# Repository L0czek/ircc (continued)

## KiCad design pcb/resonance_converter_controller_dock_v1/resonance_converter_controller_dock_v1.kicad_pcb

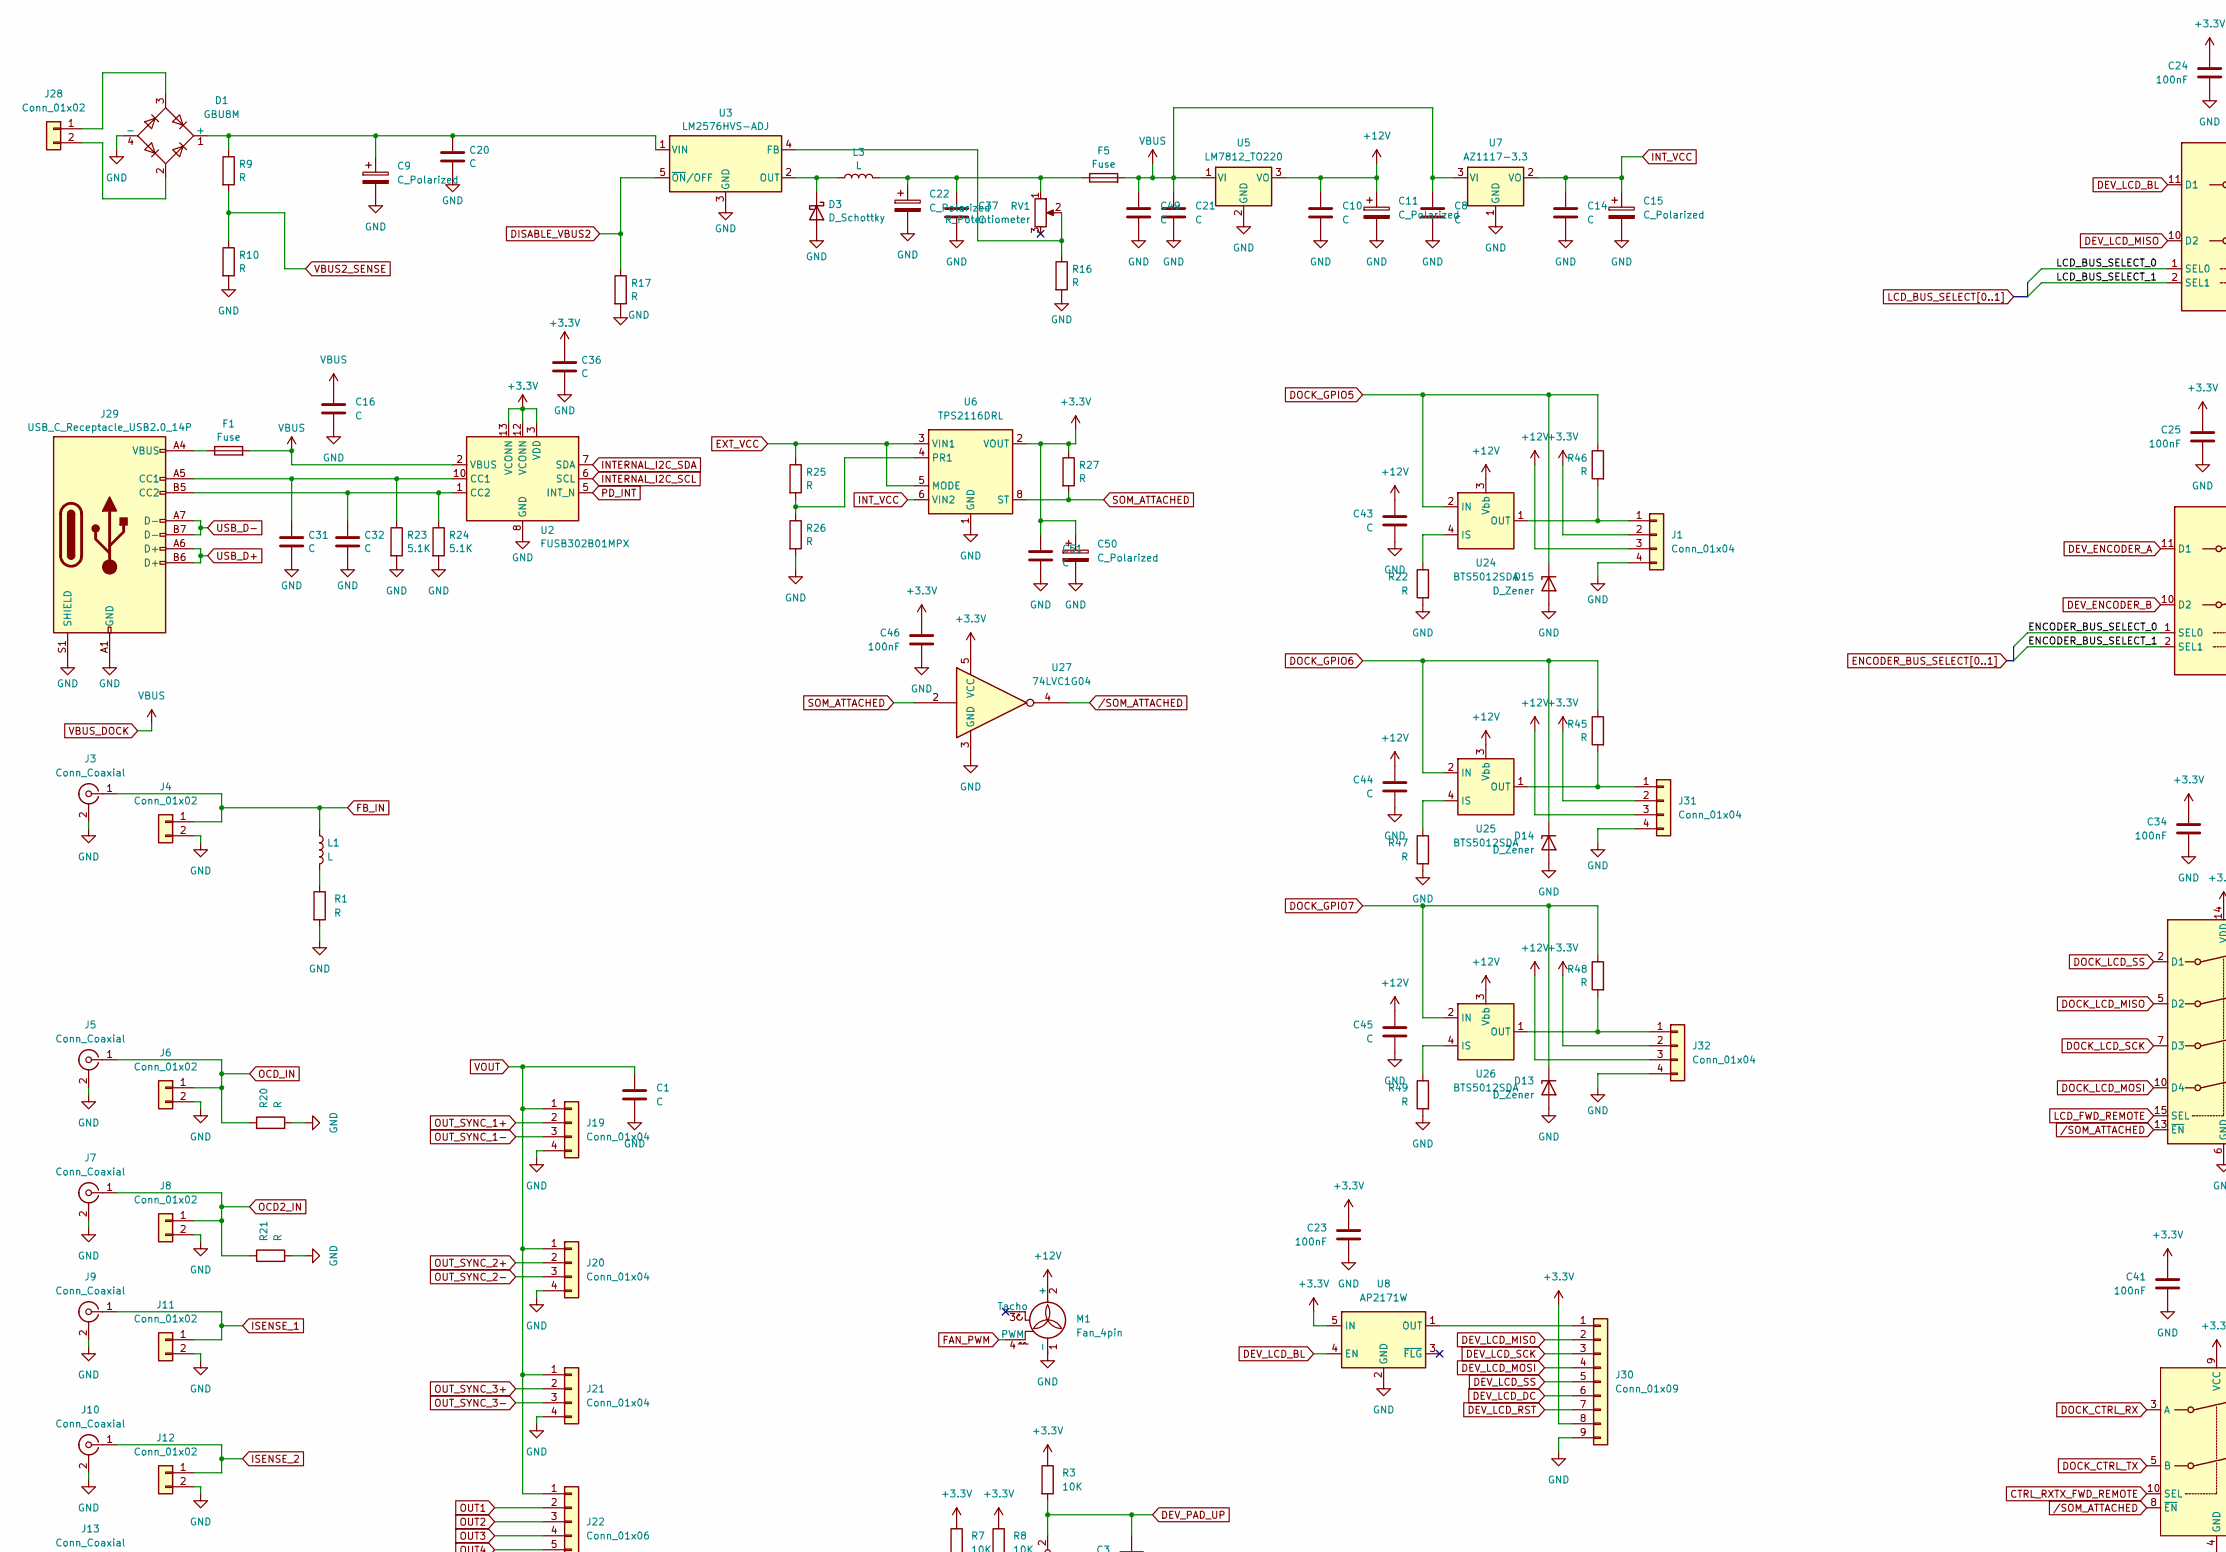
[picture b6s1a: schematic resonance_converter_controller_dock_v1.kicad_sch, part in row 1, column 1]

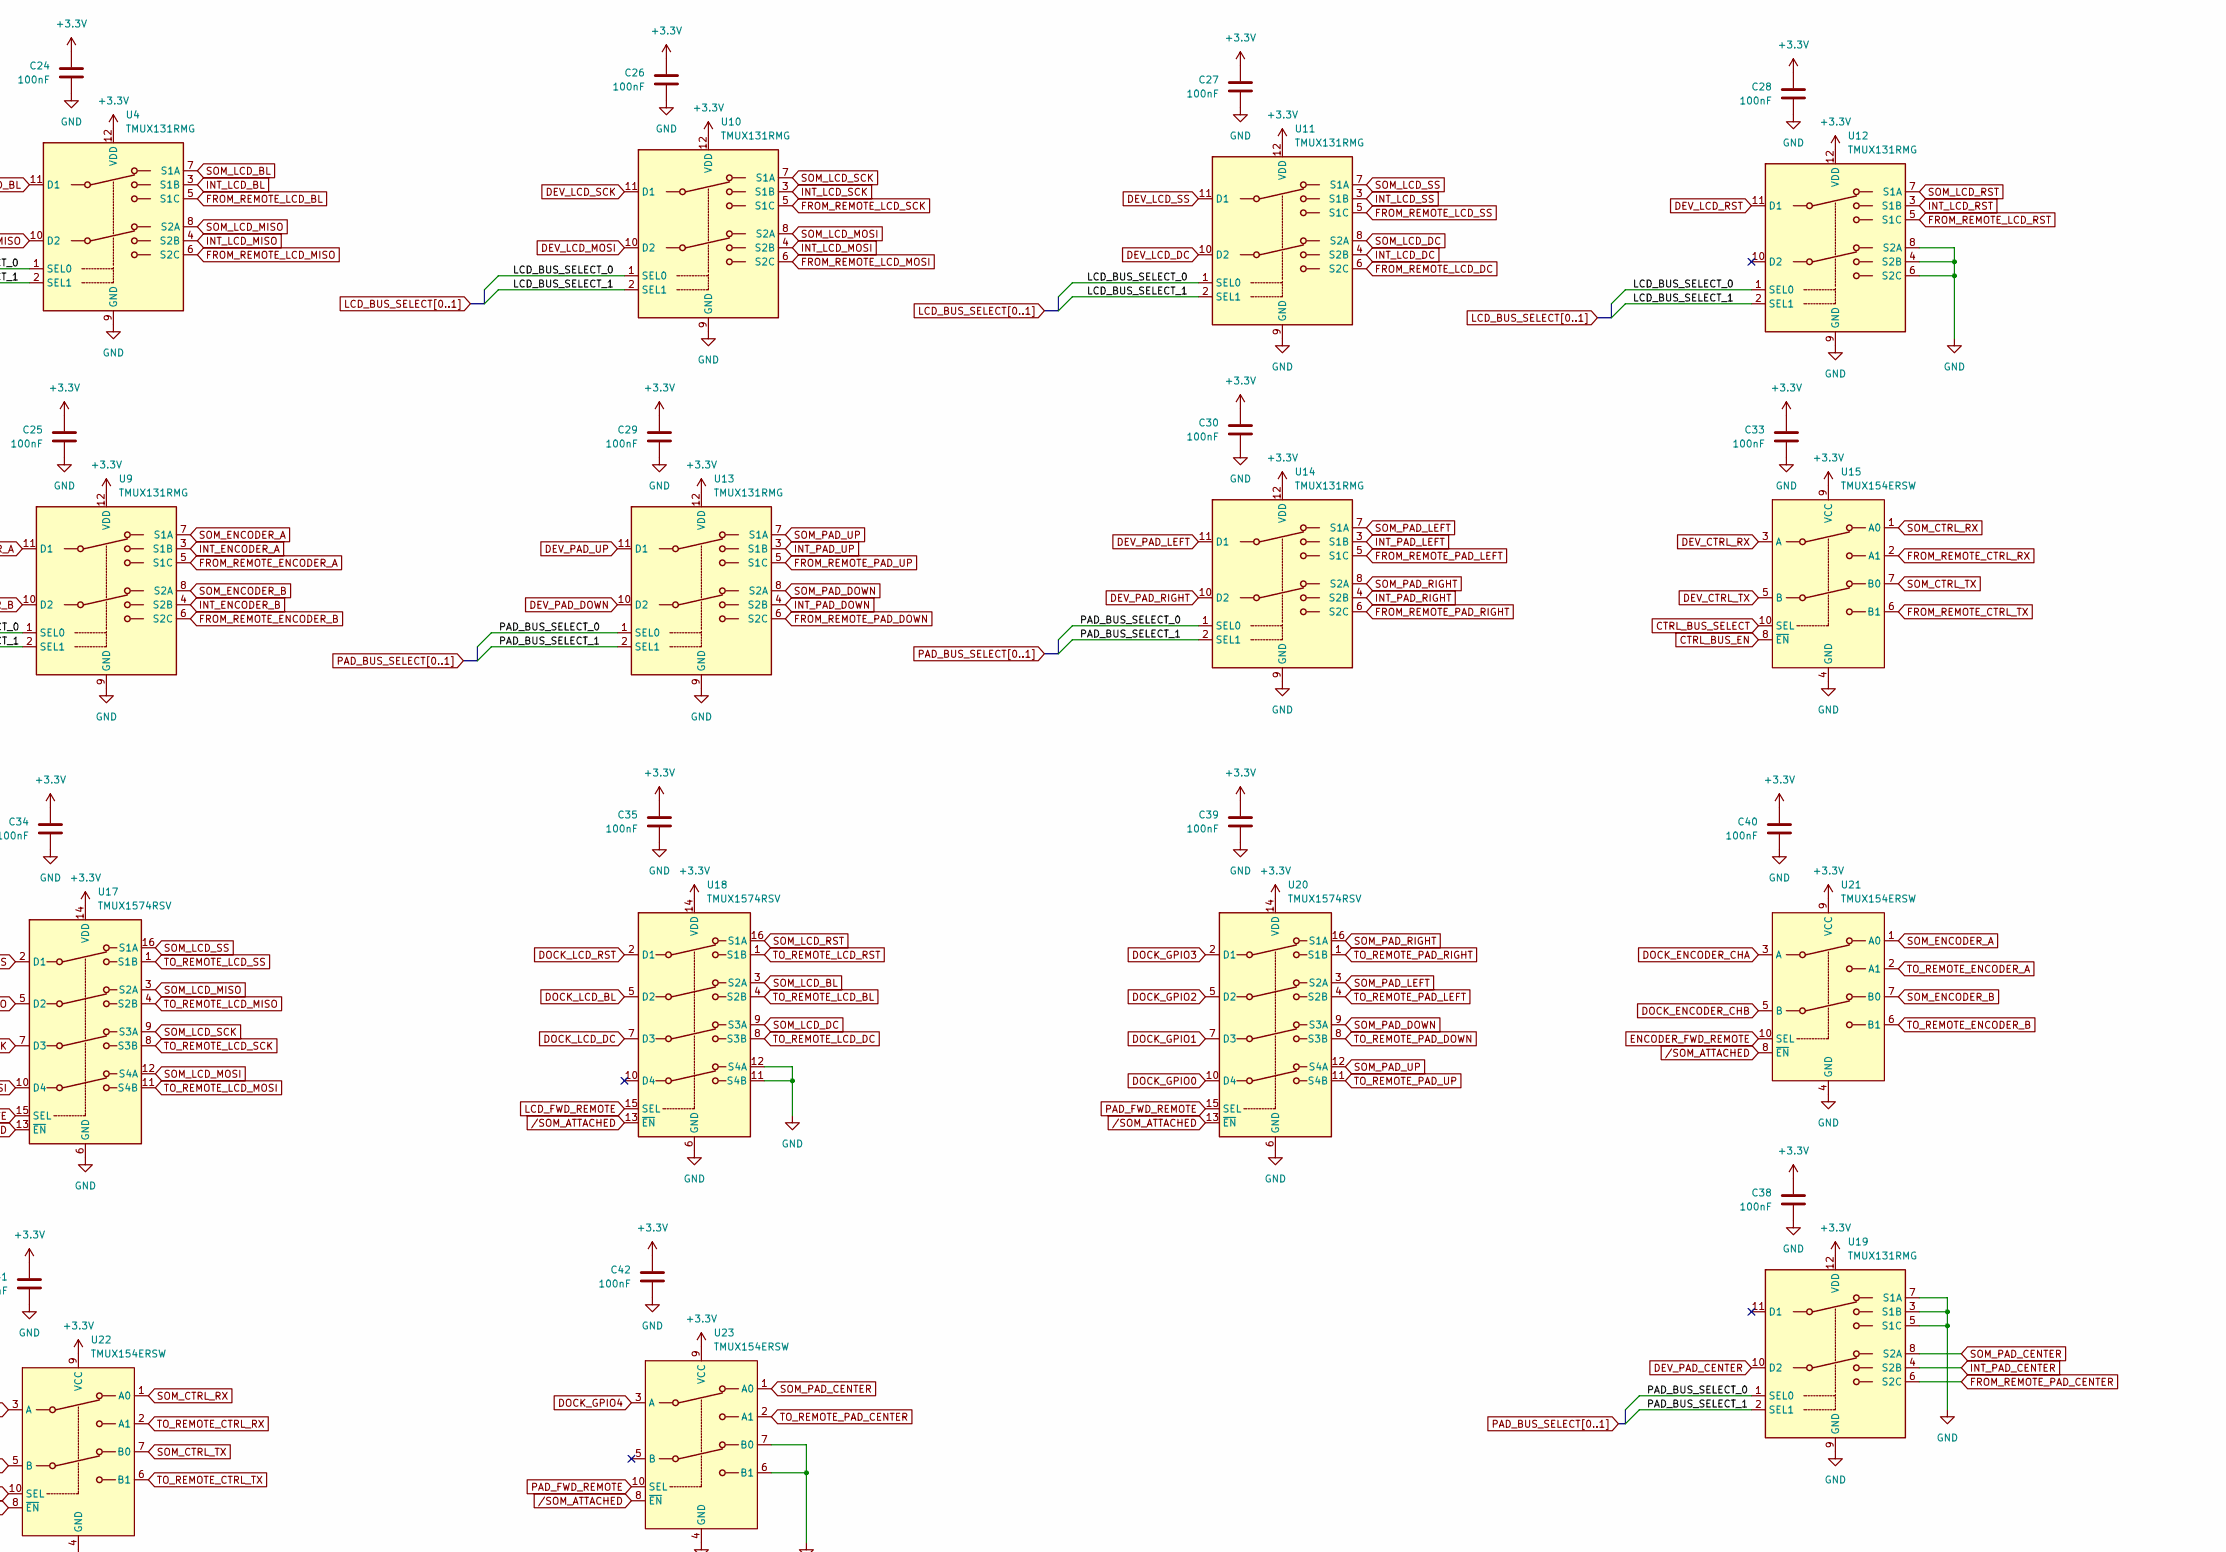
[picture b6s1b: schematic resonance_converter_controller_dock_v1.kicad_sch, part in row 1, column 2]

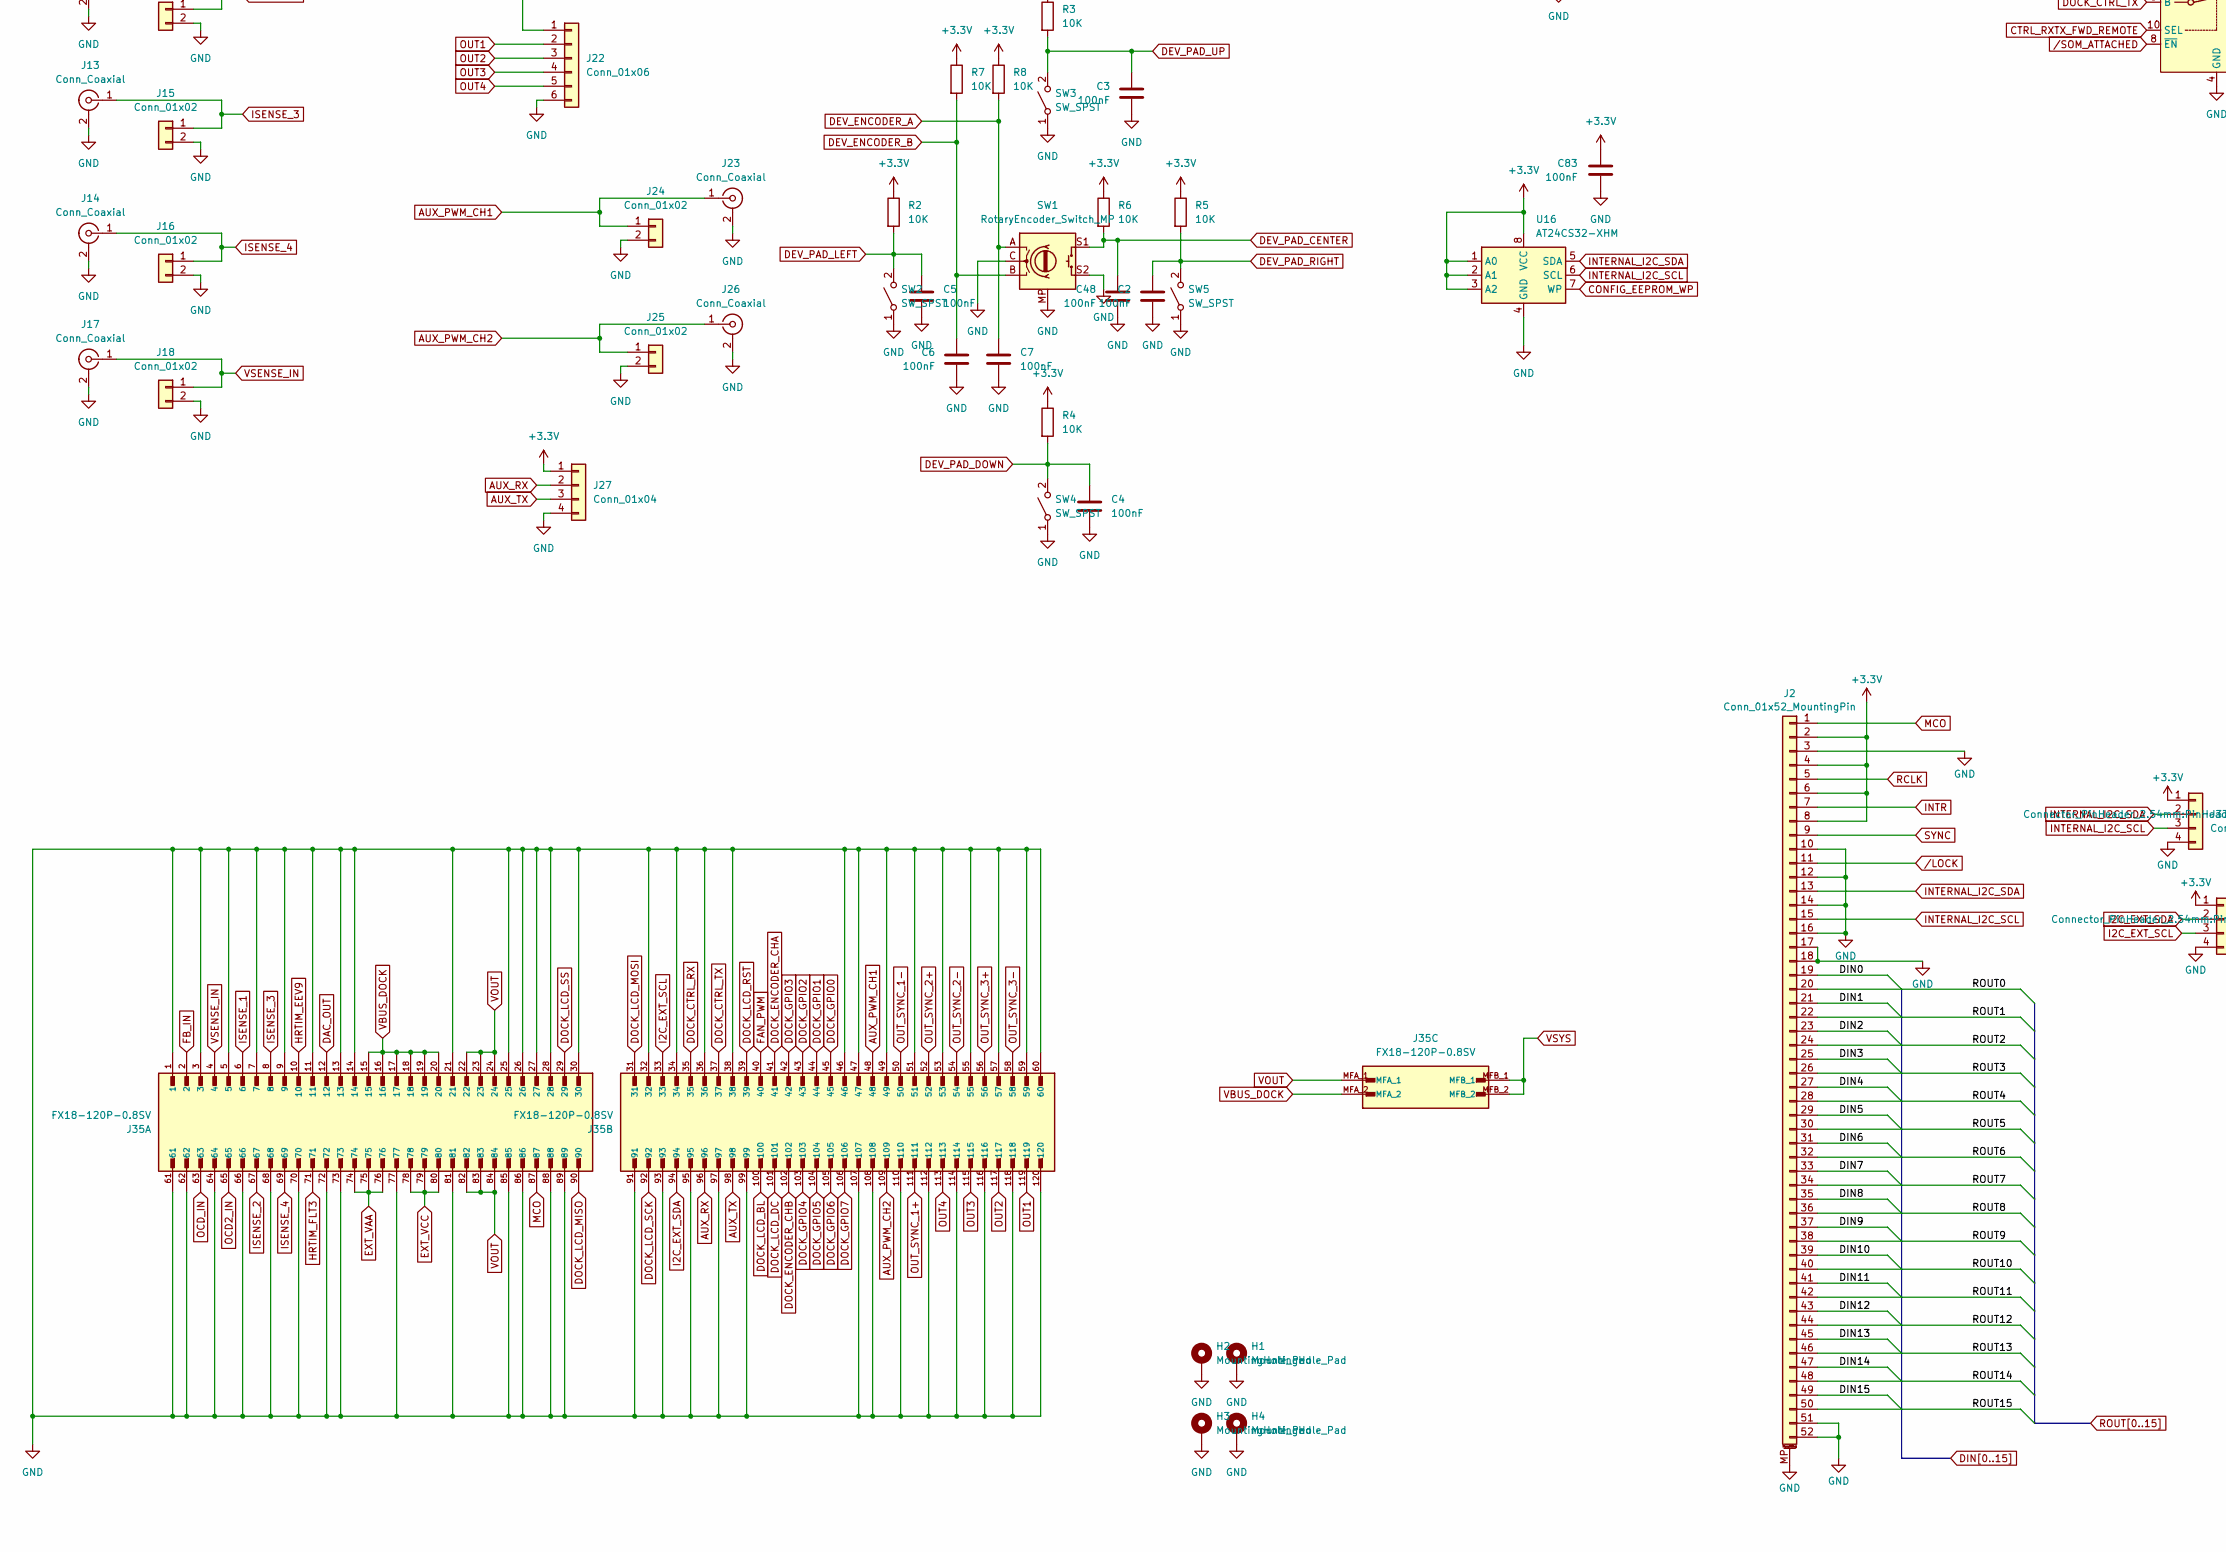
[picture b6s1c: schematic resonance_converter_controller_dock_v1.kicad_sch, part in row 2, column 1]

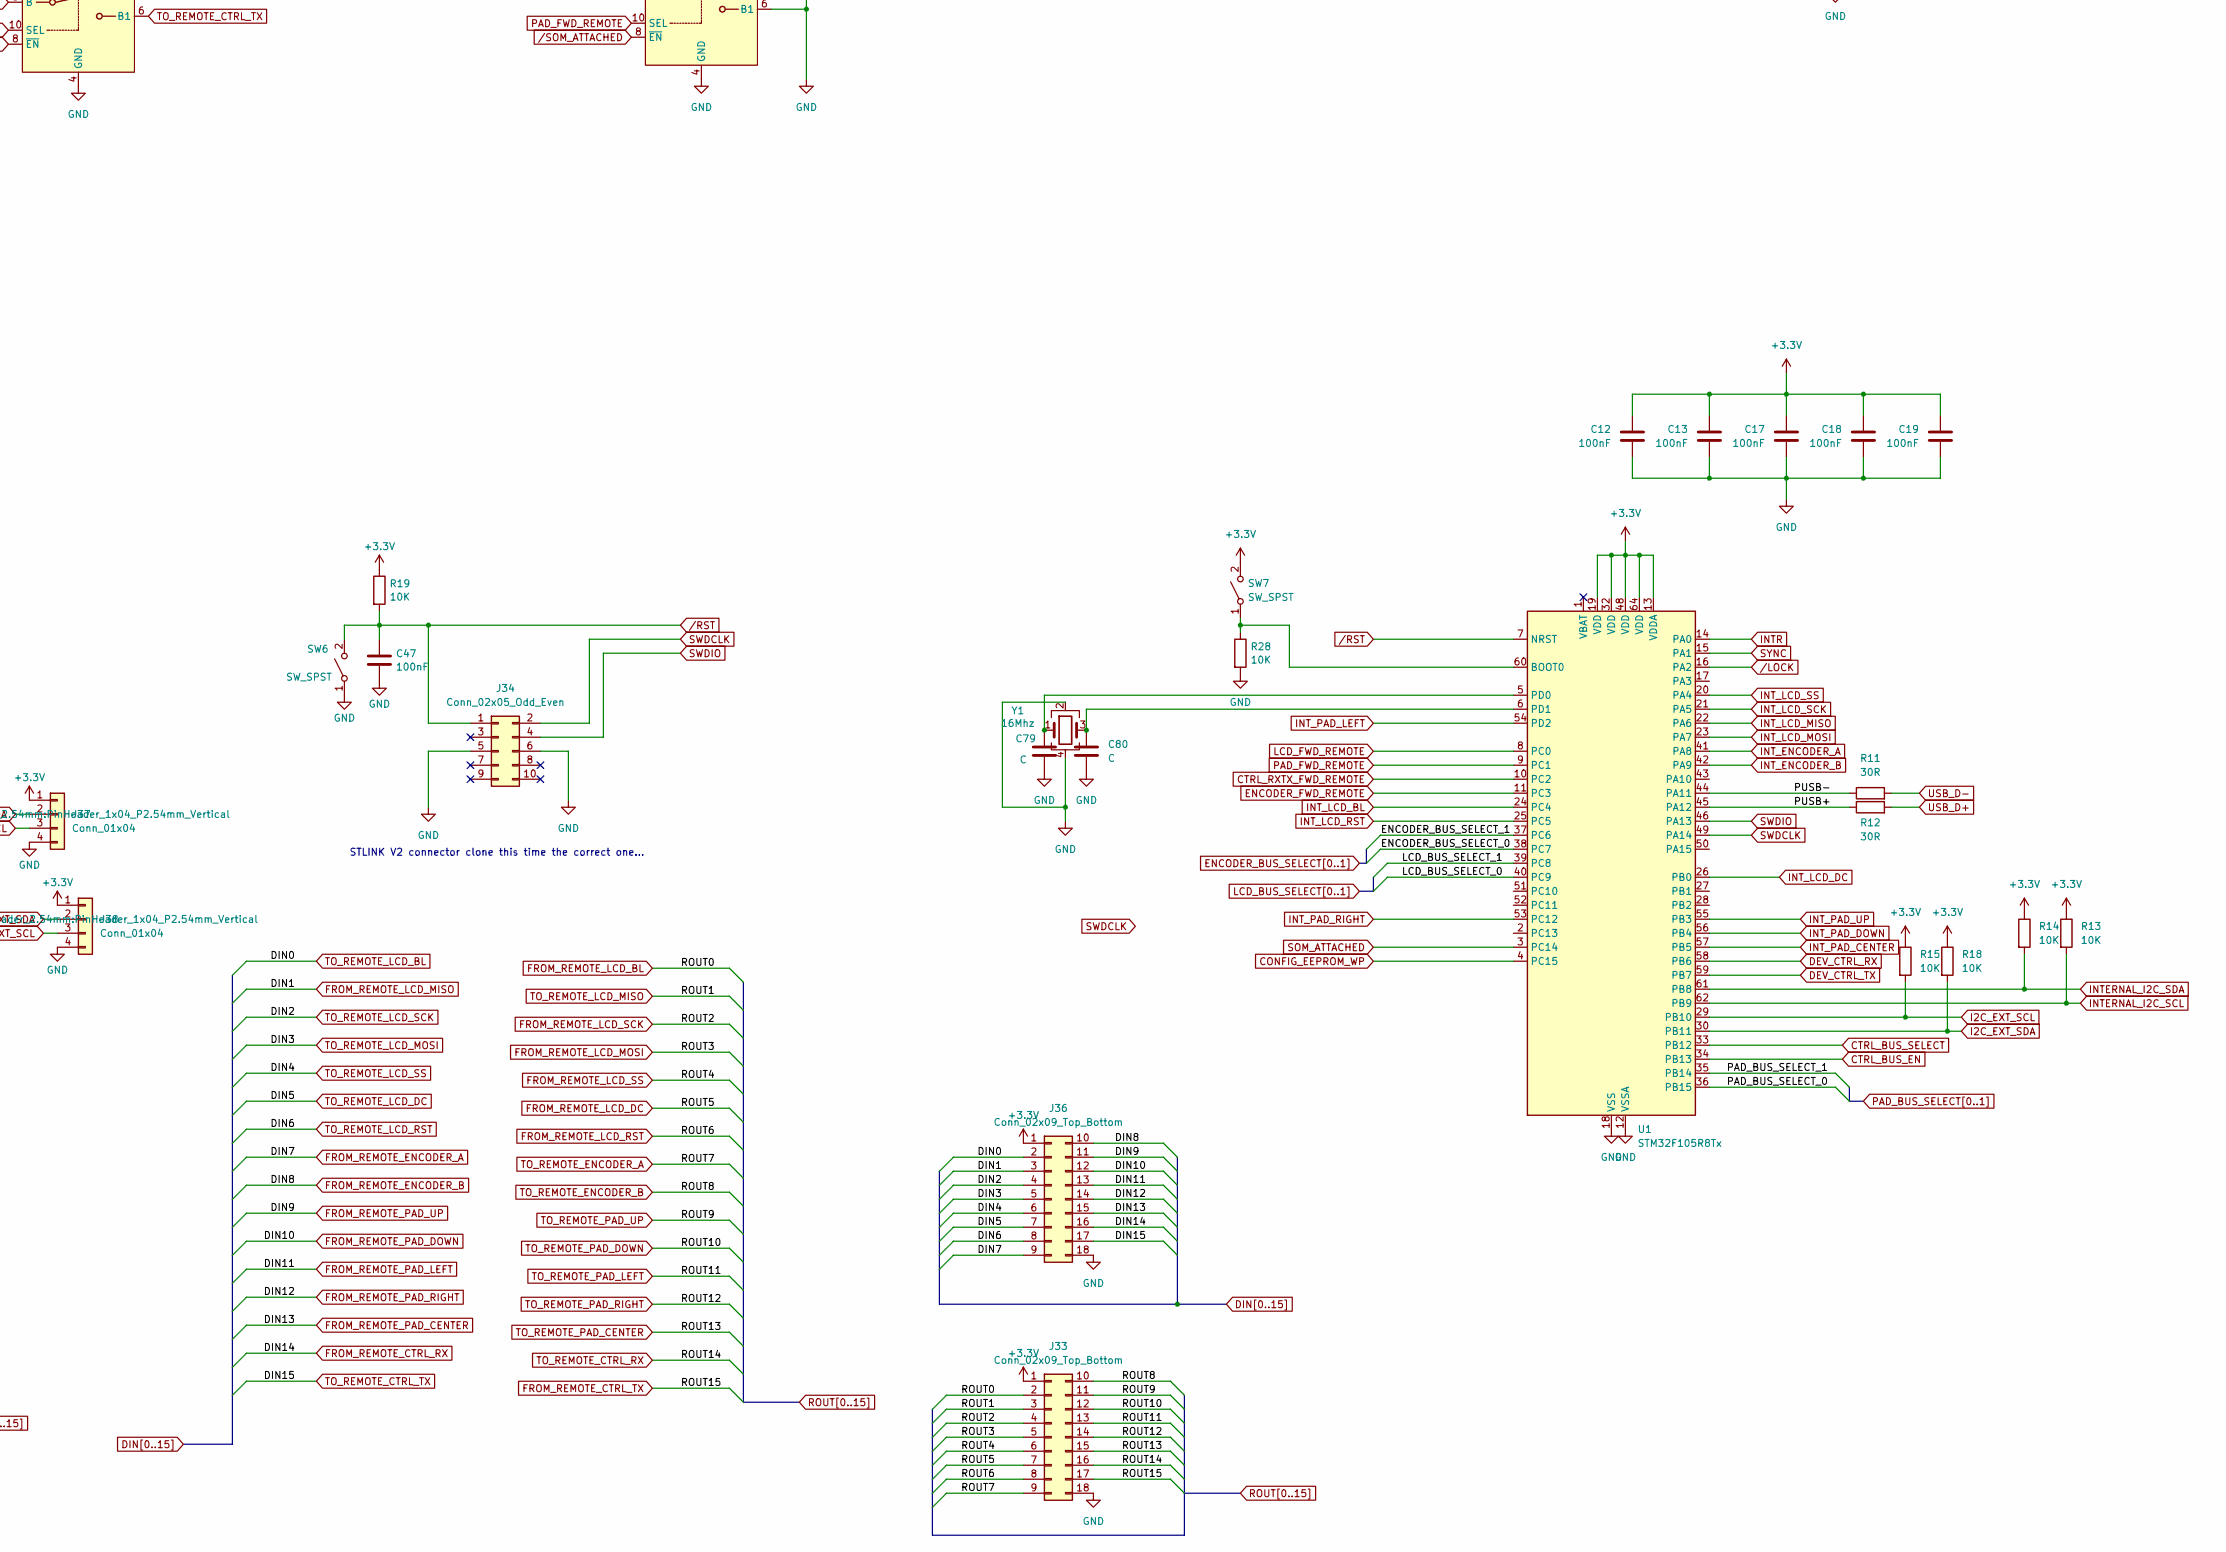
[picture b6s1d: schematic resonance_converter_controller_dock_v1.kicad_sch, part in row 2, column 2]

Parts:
C1, C16, C37, C49, C51: C; C_2220_5750Metric
C2, C3, C4, C5, C6, C7, C12, C13, C17, C18, C19, C23, C24, C25, C26, C27, C28, C29, C30, C33, C34, C35, C38, C39, C40, C41, C42, C46, C47, C48, C83: 100nF; C_0402_1005Metric
C8, C10, C14, C20, C21, C31, C32, C36, C43, C44, C45, C79, C80: C; C_0402_1005Metric
C9, C22: C_Polarized; CP_Radial_D30.0mm_P10.00mm_SnapIn
C11, C15, C50: C_Polarized; CP_Radial_D10.0mm_P5.00mm_P7.50mm
D1: GBU8M; Diode_Bridge_Vishay_GBU
D3: D_Schottky; D_SMB
D13, D14, D15: D_Zener; D_SOD-323
F1, F5: Fuse; Fuse_0805_2012Metric
H1, H2, H3, H4: MountingHole_Pad; MountingHole_3.2mm_M3_Pad_Via
J1, J19, J20, J21, J27, J31, J32: Conn_01x04; JST_PH_S4B-PH-K_1x04_P2.00mm_Horizontal
J2: Conn_01x52_MountingPin; BUS_PCI_Express_Mini_Full
J3, J5, J7, J9, J10, J13, J14, J17, J23, J26: Conn_Coaxial; SMA_Amphenol_901-143_Horizontal
J4, J6, J8, J11, J12, J15, J16, J18, J24, J25, J28: Conn_01x02; PhoenixContact_MCV_1,5_2-G-5.08_1x02_P5.08mm_Vertical
J22: Conn_01x06; JST_PH_S6B-PH-K_1x06_P2.00mm_Horizontal
J29: USB_C_Receptacle_USB2.0_14P; USB_C_Receptacle_G-Switch_GT-USB-7010ASV
J30: Conn_01x09; JST_XH_B9B-XH-AM_1x09_P2.50mm_Vertical
J33, J36: Conn_02x09_Top_Bottom; PinHeader_2x09_P2.54mm_Vertical
J34: Conn_02x05_Odd_Even; IDC-Header_2x05_P2.54mm_Vertical
J35: FX18-120P-0.8SV; HIROSE_FX18-120P-0.8SV; PARTREV 11.07.21
J37, J38: Conn_01x04; PinHeader_1x04_P2.54mm_Vertical
L1: L; L_Radial_D10.0mm_P5.00mm_Neosid_SD12k_style3
L3: L; L_Bourns_SRP1038C_10.0x10.0mm
M1: Fan_4pin; FanPinHeader_1x04_P2.54mm_Vertical
R1, R20, R21: R; R_Axial_Power_L20.0mm_W6.4mm_P22.40mm
R2, R3, R4, R5, R6, R7, R8, R13, R14, R15, R18, R19, R28: 10K; R_0402_1005Metric
R9, R10, R16, R17, R22, R25, R26, R27, R45, R46, R47, R48, R49: R; R_0402_1005Metric
R11, R12: 30R; R_0402_1005Metric
R23, R24: 5.1K; R_0402_1005Metric
RV1: R_Potentiometer; Potentiometer_Bourns_3269W_Vertical
SW1: RotaryEncoder_Switch_MP; RotaryEncoder_Alps_EC11E-Switch_Vertical_H20mm_MountingHoles
SW2, SW3, SW4, SW5: SW_SPST; SW_Cherry_MX_1.00u_PCB
SW6: SW_SPST; SW_SPST_B3S-1000
SW7: SW_SPST; SW_SPST_EVQPE1
U1: STM32F105R8Tx; LQFP-64_10x10mm_P0.5mm
U2: FUSB302B01MPX; WQFN-14-1EP_2.5x2.5mm_P0.5mm_EP1.45x1.45mm
U3: LM2576HVS-ADJ; TO-263-5_TabPin3
U4, U9, U10, U11, U12, U13, U14, U19: TMUX131RMG; Texas_RMG0012A_WQFN-12_1.8x1.8mm_P0.4mm
U5: LM7812_TO220; TO-263-2
U6: TPS2116DRL; SOT-583-8
U7: AZ1117-3.3; TO-263-2
U8: AP2171W; SOT-23-5
U15, U21, U22, U23: TMUX154ERSW; UQFN-10_1.4x1.8mm_P0.4mm
U16: AT24CS32-XHM; TSSOP-8_4.4x3mm_P0.65mm
U17, U18, U20: TMUX1574RSV; UQFN-16_1.8x2.6mm_P0.4mm
U24, U25, U26: BTS5012SDA; TO-252-4
U27: 74LVC1G04; Texas_R-PDSO-G5_DCK-5
Y1: 16Mhz; Crystal_SMD_3225-4Pin_3.2x2.5mm

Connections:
+3.3V: C12.1, C13.1, C17.1, C18.1, C19.1, C23.1, C24.1, C25.1, C26.1, C27.1, C28.1, C29.1, C30.1, C33.1, C34.1, C35.1, C36.1, C38.1, C39.1, C40.1, C41.1, C42.1, C46.1, C50.1, C51.1, C83.1, J1.2, J2.2, J2.4, J2.6, J2.8, J27.1, J30.8, J31.2, J32.2, J33.1, J36.1, J37.1, J38.1, R2.1, R3.1, R4.1, R5.1, R6.1, R7.1, R8.1, R13.1, R14.1, R15.1, R18.1, R19.1, R27.1, SW7.2 (B), U1.13 (VDDA), U1.19 (VDD), U1.32 (VDD), U1.48 (VDD), U1.64 (VDD), U2.3 (VDD), U2.4 (VDD), U2.12 (VCONN), U2.13 (VCONN), U4.12 (VDD), U6.2 (VOUT), U6.7 (VOUT), U8.5 (IN), U9.12 (VDD), U10.12 (VDD), U11.12 (VDD), U12.12 (VDD), U13.12 (VDD), U14.12 (VDD), U15.9 (VCC), U16.1 (A0), U16.2 (A1), U16.3 (A2), U16.8 (VCC), U17.14 (VDD), U18.14 (VDD), U19.12 (VDD), U20.14 (VDD), U21.9 (VCC), U22.9 (VCC), U23.9 (VCC), U27.5 (VCC)
+12V: C10.1, C11.1, C43.1, C44.1, C45.1, J1.3, J31.3, J32.3, M1.2 (+), U5.3 (VO), U24.3 (Vbb), U25.3 (Vbb), U26.3 (Vbb)
/ENCODER_BUS_SELECT_0: U1.38 (PC7), U9.1 (SEL0)
/ENCODER_BUS_SELECT_1: U1.37 (PC6), U9.2 (SEL1)
/LCD_BUS_SELECT_0: U1.40 (PC9), U4.1 (SEL0), U10.1 (SEL0), U11.1 (SEL0), U12.1 (SEL0)
/LCD_BUS_SELECT_1: U1.39 (PC8), U4.2 (SEL1), U10.2 (SEL1), U11.2 (SEL1), U12.2 (SEL1)
/PAD_BUS_SELECT_0: U1.36 (PB15), U13.1 (SEL0), U14.1 (SEL0), U19.1 (SEL0)
/PAD_BUS_SELECT_1: U1.35 (PB14), U13.2 (SEL1), U14.2 (SEL1), U19.2 (SEL1)
/PUSB+: R12.1, U1.45 (PA12)
/PUSB-: R11.1, U1.44 (PA11)
AUX_PWM_CH1: J23.1 (In), J24.1, J35.48
AUX_PWM_CH2: J25.1, J26.1 (In), J35.109
AUX_RX: J27.2, J35.96
AUX_TX: J27.3, J35.98
CONFIG_EEPROM_WP: U1.4 (PC15), U16.7 (WP)
CTRL_BUS_EN: U1.34 (PB13), U15.8 (~EN)
CTRL_BUS_SELECT: U1.33 (PB12), U15.10 (SEL)
CTRL_RXTX_FWD_REMOTE: U1.10 (PC2), U22.10 (SEL)
DAC_OUT: J35.12
DEV_CTRL_RX: U1.58 (PB6), U15.3 (A)
DEV_CTRL_TX: U1.59 (PB7), U15.5 (B)
DEV_ENCODER_A: C7.1, R8.2, SW1.A, U9.11 (D1)
DEV_ENCODER_B: C6.1, R7.2, SW1.B, U9.10 (D2)
DEV_LCD_BL: U4.11 (D1), U8.4 (EN)
DEV_LCD_DC: J30.6, U11.10 (D2)
DEV_LCD_MISO: J30.2, U4.10 (D2)
DEV_LCD_MOSI: J30.4, U10.10 (D2)
DEV_LCD_RST: J30.7, U12.11 (D1)
DEV_LCD_SCK: J30.3, U10.11 (D1)
DEV_LCD_SS: J30.5, U11.11 (D1)
DEV_PAD_CENTER: C48.1, R6.2, SW1.S1, U19.10 (D2)
DEV_PAD_DOWN: C4.1, R4.2, SW4.2 (B), U13.10 (D2)
DEV_PAD_LEFT: C5.1, R2.2, SW2.2 (B), U14.11 (D1)
DEV_PAD_RIGHT: C2.1, R5.2, SW5.2 (B), U14.10 (D2)
DEV_PAD_UP: C3.1, R3.2, SW3.2 (B), U13.11 (D1)
DISABLE_VBUS2: R17.1, U3.5 (~ON/OFF)
DOCK_CTRL_RX: J35.35, U22.3 (A)
DOCK_CTRL_TX: J35.37, U22.5 (B)
DOCK_ENCODER_CHA: J35.41, U21.3 (A)
DOCK_ENCODER_CHB: J35.102, U21.5 (B)
DOCK_GPIO0: J35.45, U20.10 (D4)
DOCK_GPIO1: J35.44, U20.7 (D3)
DOCK_GPIO2: J35.43, U20.5 (D2)
DOCK_GPIO3: J35.42, U20.2 (D1)
DOCK_GPIO4: J35.103, U23.3 (A)
DOCK_GPIO5: D15.1 (K), J35.104, R46.1, U24.2 (IN)
DOCK_GPIO6: D14.1 (K), J35.105, R45.1, U25.2 (IN)
DOCK_GPIO7: D13.1 (K), J35.106, R48.1, U26.2 (IN)
DOCK_LCD_BL: J35.100, U18.5 (D2)
DOCK_LCD_DC: J35.101, U18.7 (D3)
DOCK_LCD_MISO: J35.90, U17.5 (D2)
DOCK_LCD_MOSI: J35.31, U17.10 (D4)
DOCK_LCD_RST: J35.39, U18.2 (D1)
DOCK_LCD_SCK: J35.92, U17.7 (D3)
DOCK_LCD_SS: J35.29, U17.2 (D1)
ENCODER_FWD_REMOTE: U1.11 (PC3), U21.10 (SEL)
EXT_VAA: J35.74, J35.75, J35.76
EXT_VCC: J35.78, J35.79, J35.80, R25.1, U6.3 (VIN1), U6.5 (MODE)
FAN_PWM: J35.40, M1.4 (PWM)
FB_IN: J3.1 (In), J4.1, J35.2, L1.1
FROM_REMOTE_CTRL_RX: J2.47, J36.16, U15.2 (A1)
FROM_REMOTE_CTRL_TX: J2.50, J33.17, U15.6 (B1)
FROM_REMOTE_ENCODER_A: J2.33, J36.9, U9.5 (S1C)
FROM_REMOTE_ENCODER_B: J2.35, J36.10, U9.6 (S2C)
FROM_REMOTE_LCD_BL: J2.20, J33.2, U4.5 (S1C)
FROM_REMOTE_LCD_DC: J2.30, J33.7, U11.6 (S2C)
FROM_REMOTE_LCD_MISO: J2.21, J36.3, U4.6 (S2C)
FROM_REMOTE_LCD_MOSI: J2.26, J33.5, U10.6 (S2C)
FROM_REMOTE_LCD_RST: J2.32, J33.8, U12.5 (S1C)
FROM_REMOTE_LCD_SCK: J2.24, J33.4, U10.5 (S1C)
FROM_REMOTE_LCD_SS: J2.28, J33.6, U11.5 (S1C)
FROM_REMOTE_PAD_CENTER: J2.45, J36.15, U19.6 (S2C)
FROM_REMOTE_PAD_DOWN: J2.39, J36.12, U13.6 (S2C)
FROM_REMOTE_PAD_LEFT: J2.41, J36.13, U14.5 (S1C)
FROM_REMOTE_PAD_RIGHT: J2.43, J36.14, U14.6 (S2C)
FROM_REMOTE_PAD_UP: J2.37, J36.11, U13.5 (S1C)
GND: C1.2, C2.2, C3.2, C4.2, C5.2, C6.2, C7.2, C8.2, C9.2, C10.2, C11.2, C12.2, C13.2, C14.2, C15.2, C16.2, C17.2, C18.2, C19.2, C20.2, C21.2, C22.2, C23.2, C24.2, C25.2, C26.2, C27.2, C28.2, C29.2, C30.2, C31.2, C32.2, C33.2, C34.2, C35.2, C36.2, C37.2, C38.2, C39.2, C40.2, C41.2, C42.2, C43.2, C44.2, C45.2, C46.2, C47.2, C48.2, C49.2, C50.2, C51.2, C79.2, C80.2, C83.2, D1.4 (-), D3.2 (A), D13.2 (A), D14.2 (A), D15.2 (A), H1.1, H2.1, H3.1, H4.1, J1.4, J2.3, J2.10, J2.12, J2.14, J2.16, J2.17, J2.18, J2.51, J2.52, J2.MP (MountPin), J3.2 (Ext), J4.2, J5.2 (Ext), J6.2, J7.2 (Ext), J8.2, J9.2 (Ext), J10.2 (Ext), J11.2, J12.2, J13.2 (Ext), J14.2 (Ext), J15.2, J16.2, J17.2 (Ext), J18.2, J19.4, J20.4, J21.4, J22.6, J23.2 (Ext), J24.2, J25.2, J26.2 (Ext), J27.4, J29.A1 (GND), J29.A12 (GND), J29.B1 (GND), J29.B12 (GND), J29.S1 (SHIELD), J30.9, J31.4, J32.4, J33.18, J34.5, J34.6, J35.1, J35.3, J35.5, J35.7, J35.9, J35.11, J35.13, J35.14, J35.21, J35.25, J35.26, J35.27, J35.28, J35.30, J35.32, J35.34, J35.36, J35.38, J35.46, J35.47, J35.49, J35.51, J35.53, J35.55, J35.57, J35.59, J35.60, J35.61, J35.62, J35.64, J35.66, J35.68, J35.70, J35.72, J35.73, J35.77, J35.81, J35.85, J35.86, J35.88, J35.89, J35.91, J35.93, J35.95, J35.97, J35.99, J35.107, J35.108, J35.110, J35.112, J35.114, J35.116, J35.118, J35.120, J36.18, J37.4, J38.4, M1.1 (-), R1.2, R10.2, R16.2, R17.2, R20.2, R21.2, R22.2, R23.2, R24.2, R26.2, R28.2, R47.2, R49.2, SW1.C, SW1.MP, SW1.S2, SW2.1 (A), SW3.1 (A), SW4.1 (A), SW5.1 (A), SW6.1 (A), U1.12 (VSSA), U1.18 (VSS), U1.31 (VSS), U1.47 (VSS), U1.63 (VSS), U2.8 (GND), U2.9 (GND), U2.15 (GND), U3.3 (GND), U4.9 (GND), U5.2 (GND), U6.1 (GND), U7.1 (GND), U8.2 (GND), U9.9 (GND), U10.9 (GND), U11.9 (GND), U12.4 (S2B), U12.6 (S2C), U12.8 (S2A), U12.9 (GND), U13.9 (GND), U14.9 (GND), U15.4 (GND), U16.4 (GND), U17.6 (GND), U18.6 (GND), U18.11 (S4B), U18.12 (S4A), U19.3 (S1B), U19.5 (S1C)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
HRTIM_EEV9: J35.10
HRTIM_FLT3: J35.71
I2C_EXT_SCL: J35.33, J38.3, R15.2, U1.29 (PB10)
I2C_EXT_SDA: J35.94, J38.2, R18.2, U1.30 (PB11)
INTERNAL_I2C_SCL: J2.15, J37.3, R13.2, U1.62 (PB9), U2.6 (SCL), U16.6 (SCL)
INTERNAL_I2C_SDA: J2.13, J37.2, R14.2, U1.61 (PB8), U2.7 (SDA), U16.5 (SDA)
INTR: J2.7, U1.14 (PA0)
INT_ENCODER_A: U1.41 (PA8), U9.3 (S1B)
INT_ENCODER_B: U1.42 (PA9), U9.4 (S2B)
INT_LCD_BL: U1.24 (PC4), U4.3 (S1B)
INT_LCD_DC: U1.26 (PB0), U11.4 (S2B)
INT_LCD_MISO: U1.22 (PA6), U4.4 (S2B)
INT_LCD_MOSI: U1.23 (PA7), U10.4 (S2B)
INT_LCD_RST: U1.25 (PC5), U12.3 (S1B)
INT_LCD_SCK: U1.21 (PA5), U10.3 (S1B)
INT_LCD_SS: U1.20 (PA4), U11.3 (S1B)
INT_PAD_CENTER: U1.57 (PB5), U19.4 (S2B)
INT_PAD_DOWN: U1.56 (PB4), U13.4 (S2B)
INT_PAD_LEFT: U1.54 (PD2), U14.3 (S1B)
INT_PAD_RIGHT: U1.53 (PC12), U14.4 (S2B)
INT_PAD_UP: U1.55 (PB3), U13.3 (S1B)
INT_VCC: C14.1, C15.1, U6.6 (VIN2), U7.2 (VO)
ISENSE_1: J9.1 (In), J11.1, J35.6
ISENSE_2: J10.1 (In), J12.1, J35.67
ISENSE_3: J13.1 (In), J15.1, J35.8
ISENSE_4: J14.1 (In), J16.1, J35.69
LCD_FWD_REMOTE: U1.8 (PC0), U17.15 (SEL), U18.15 (SEL)
MCO: J2.1, J35.87
unnamed: C22.1, C37.1, F5.1, L3.2, RV1.1
unnamed: C9.1, C20.1, D1.1 (+), R9.1, U3.1 (VIN)
unnamed: D3.1 (K), L3.1, U3.2 (OUT)
unnamed: F1.1, J29.A4 (VBUS), J29.A9 (VBUS), J29.B4 (VBUS), J29.B9 (VBUS)
unnamed: J1.1, R46.2, U24.1 (OUT), U24.5 (OUT)
unnamed: D1.3, J28.1
unnamed: D1.2, J28.2
unnamed: C31.1, J29.A5 (CC1), R23.1, U2.10 (CC1), U2.11 (CC1)
unnamed: C32.1, J29.B5 (CC2), R24.1, U2.1 (CC2), U2.14 (CC2)
unnamed: J30.1, U8.1 (OUT)
unnamed: J31.1, R45.2, U25.1 (OUT), U25.5 (OUT)
unnamed: J32.1, R48.2, U26.1 (OUT), U26.5 (OUT)
unnamed: L1.2, R1.1
unnamed: R28.1, SW7.1 (A), U1.60 (BOOT0)
unnamed: C79.1, U1.5 (PD0), Y1.1
unnamed: C80.1, U1.6 (PD1), Y1.3
unnamed: R16.1, RV1.2, U3.4 (FB)
unnamed: R25.2, R26.1, U6.4 (PR1)
unnamed: R22.1, U24.4 (IS)
unnamed: R47.1, U25.4 (IS)
unnamed: R49.1, U26.4 (IS)
OCD2_IN: J7.1 (In), J8.1, J35.65, R21.1
OCD_IN: J5.1 (In), J6.1, J35.63, R20.1
OUT1: J22.2, J35.119
OUT2: J22.3, J35.117
OUT3: J22.4, J35.115
OUT4: J22.5, J35.113
OUT_SYNC_1+: J19.2, J35.111
OUT_SYNC_1-: J19.3, J35.50
OUT_SYNC_2+: J20.2, J35.52
OUT_SYNC_2-: J20.3, J35.54
OUT_SYNC_3+: J21.2, J35.56
OUT_SYNC_3-: J21.3, J35.58
PAD_FWD_REMOTE: U1.9 (PC1), U20.15 (SEL), U23.10 (SEL)
PD_INT: U2.5 (INT_N)
RCLK: J2.5
SOM_ATTACHED: R27.2, U1.3 (PC14), U6.8 (ST), U27.2
SOM_CTRL_RX: U15.1 (A0), U22.1 (A0)
SOM_CTRL_TX: U15.7 (B0), U22.7 (B0)
SOM_ENCODER_A: U9.7 (S1A), U21.1 (A0)
SOM_ENCODER_B: U9.8 (S2A), U21.7 (B0)
SOM_LCD_BL: U4.7 (S1A), U18.3 (S2A)
SOM_LCD_DC: U11.8 (S2A), U18.9 (S3A)
SOM_LCD_MISO: U4.8 (S2A), U17.3 (S2A)
SOM_LCD_MOSI: U10.8 (S2A), U17.12 (S4A)
SOM_LCD_RST: U12.7 (S1A), U18.16 (S1A)
SOM_LCD_SCK: U10.7 (S1A), U17.9 (S3A)
SOM_LCD_SS: U11.7 (S1A), U17.16 (S1A)
SOM_PAD_CENTER: U19.8 (S2A), U23.1 (A0)
SOM_PAD_DOWN: U13.8 (S2A), U20.9 (S3A)
SOM_PAD_LEFT: U14.7 (S1A), U20.3 (S2A)
SOM_PAD_RIGHT: U14.8 (S2A), U20.16 (S1A)
SOM_PAD_UP: U13.7 (S1A), U20.12 (S4A)
SWDCLK: J34.2, U1.49 (PA14)
SWDIO: J34.4, U1.46 (PA13)
SYNC: J2.9, U1.15 (PA1)
TO_REMOTE_CTRL_RX: J2.48, J33.16, U22.2 (A1)
TO_REMOTE_CTRL_TX: J2.49, J36.17, U22.6 (B1)
TO_REMOTE_ENCODER_A: J2.34, J33.9, U21.2 (A1)
TO_REMOTE_ENCODER_B: J2.36, J33.10, U21.6 (B1)
TO_REMOTE_LCD_BL: J2.19, J36.2, U18.4 (S2B)
TO_REMOTE_LCD_DC: J2.29, J36.7, U18.8 (S3B)
TO_REMOTE_LCD_MISO: J2.22, J33.3, U17.4 (S2B)
TO_REMOTE_LCD_MOSI: J2.25, J36.5, U17.11 (S4B)
TO_REMOTE_LCD_RST: J2.31, J36.8, U18.1 (S1B)
TO_REMOTE_LCD_SCK: J2.23, J36.4, U17.8 (S3B)
TO_REMOTE_LCD_SS: J2.27, J36.6, U17.1 (S1B)
TO_REMOTE_PAD_CENTER: J2.46, J33.15, U23.2 (A1)
TO_REMOTE_PAD_DOWN: J2.40, J33.12, U20.8 (S3B)
TO_REMOTE_PAD_LEFT: J2.42, J33.13, U20.4 (S2B)
TO_REMOTE_PAD_RIGHT: J2.44, J33.14, U20.1 (S1B)
TO_REMOTE_PAD_UP: J2.38, J33.11, U20.11 (S4B)
USB_D+: J29.A6 (D+), J29.B6 (D+), R12.2
USB_D-: J29.A7 (D-), J29.B7 (D-), R11.2
VBUS2_SENSE: R9.2, R10.1
VBUS_DOCK: C8.1, C16.1, C21.1, C49.1, F1.2, F5.2, J35.15, J35.16, J35.17, J35.18, J35.19, J35.20, J35.MFA_2, U2.2 (VBUS), U5.1 (VI), U7.3 (VI)
VOUT: C1.1, J19.1, J20.1, J21.1, J22.1, J35.22, J35.23, J35.24, J35.82, J35.83, J35.84, J35.MFA_1
VSENSE_IN: J17.1 (In), J18.1, J35.4
VSYS: J35.MFB_1, J35.MFB_2
/LOCK: J2.11, U1.16 (PA2)
/RST: C47.1, J34.1, R19.2, SW6.2 (B), U1.7 (NRST)
/SOM_ATTACHED: U17.13 (~EN), U18.13 (~EN), U20.13 (~EN), U21.8 (~EN), U22.8 (~EN), U23.8 (~EN), U27.4

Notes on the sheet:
STLINK V2 connector clone this time the correct one...

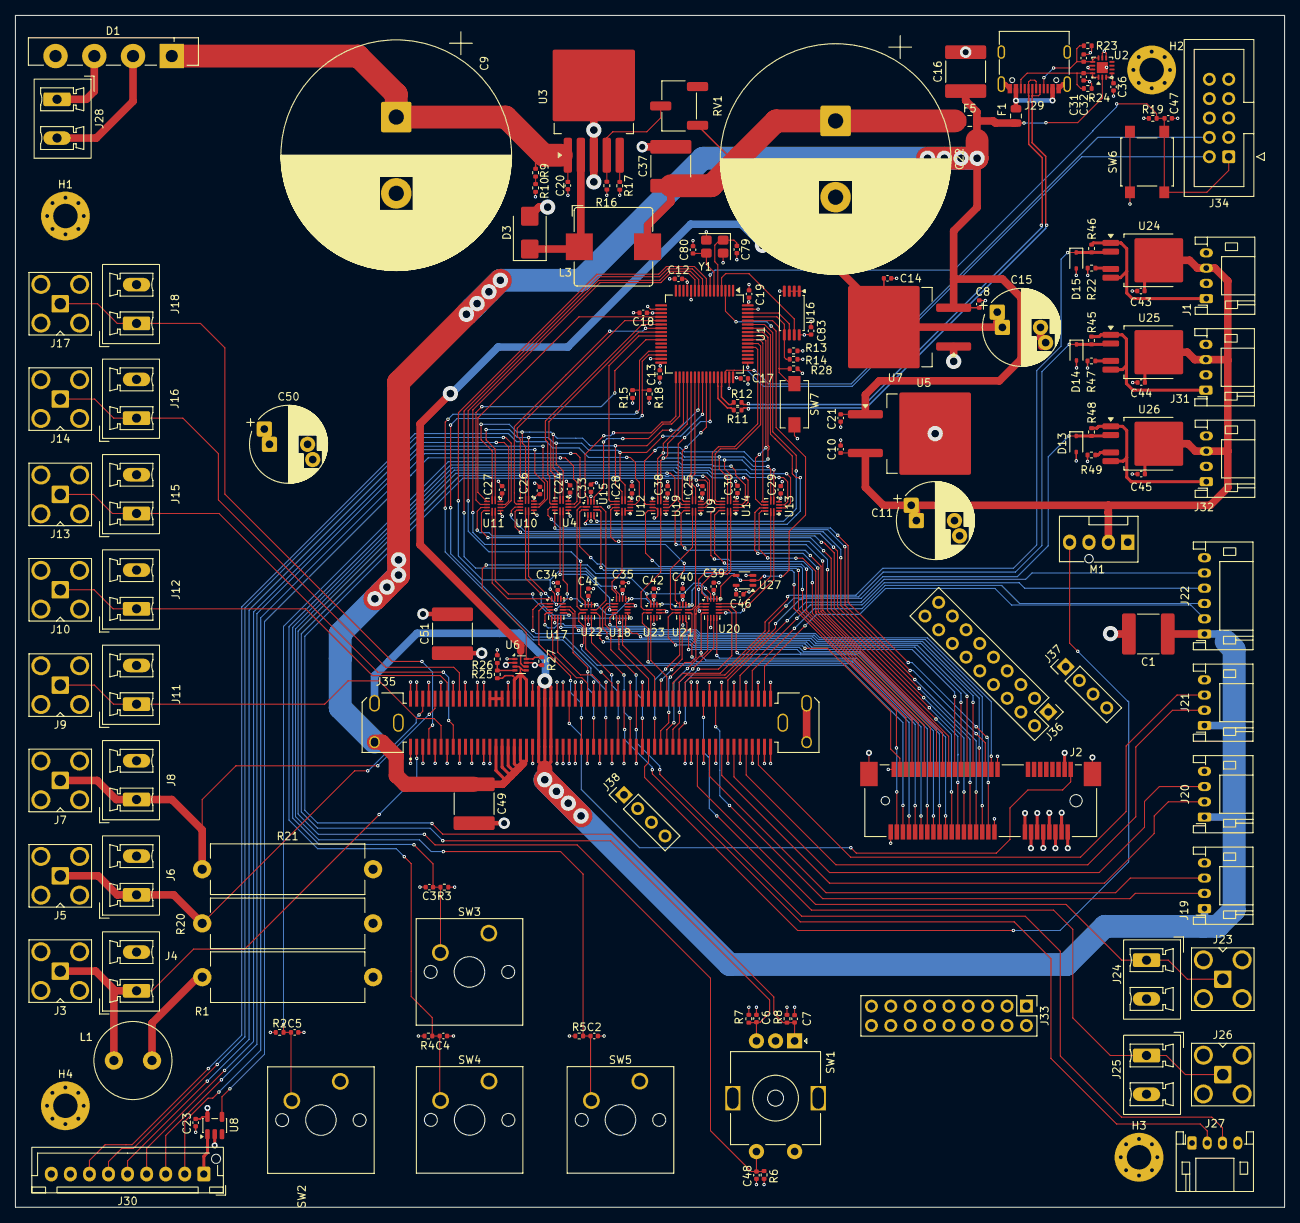
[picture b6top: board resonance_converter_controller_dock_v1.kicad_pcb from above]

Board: 4 copper layers, 166.4 x 156.2 mm, 175 parts (0 on the bottom side), 182 nets.
